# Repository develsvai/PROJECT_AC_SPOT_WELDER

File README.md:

## AC_SPOT_WELDER - 기술 분석 및 펌웨어 리팩토링

- **프로젝트 명:** 자동 트리거 기능의 AC 스팟 용접기
- **분석 대상:** 하드웨어(회로, PCB) 및 펌웨어 코드
- **문서 목적:** 원본 프로젝트의 기술적 구현 상태를 분석하고, 식별된 문제점에 대한 개선 방안과 그에 따른 최종 개선 코드를 제시함.
- 단 현재로써는 적용시킬수 있는 환경 및 조건이 안됨, 코드 관점에서의 분석

---

### **Part A. 펌웨어 코드 주요 개선점**

원본 코드는 기능 구현에 집중한 '유기체적' 코드이며, 개선된 코드는 안정성, 확장성, 유지보수성을 확보하기 위한 설계 원칙을 적용한 '구조적' 코드입니다. 각 개선점을 원본 코드와 개선된 코드의 실제 예시를 통해 비교 분석합니다.

### **1. 타이밍 제어 방식의 변경: `delay`에서 `하드웨어 타이머`로**

- **이전 코드:** 모든 시간 제어를 `delay_ms()`에 의존하며, 특히 ISR(인터럽트 서비스 루틴) 컨텍스트에서 CPU를 정지시키는 블로킹(Blocking) 방식을 사용함. 이는 시스템 반응성 저하의 주요 원인이 되는 구조적 문제점이다.

```c
// [원본 코드] ISR 내부에서 직접 delay 호출
ISR(INT0_vect)
{
    if(isr_cn == 1 & vbl>=8){
        _delay_ms(0.5);
         PORTC = 0x20; // 트리거 ON
         // CPU가 여기서 멈춰서 다음 라인으로 넘어가지 않음
         delay_ms(spot_time_hz * halfcycle); 
         PORTC = 0x00; // 트리거 OFF
         delay_ms(nbl);
         isr_cn=0;
    } 
    // ...
}
```

- **개선된 코드:** 하드웨어 Timer1을 이용해 1ms 주기의 시스템 틱(Tick)을 생성하고, 모든 시간 계산을 논블로킹(Non-blocking) 방식으로 처리함. 이를 통해 시스템은 다른 입력에 항상 반응할 수 있는 상태를 유지한다.

```c
// [개선된 코드] ISR은 플래그만 설정하고, 타이머가 시간 관리
volatile uint16_t weld_pulse_timer_ms;

// 1ms 마다 실행되는 타이머 ISR
ISR(TIMER1_COMPA_vect) {
    if (weld_pulse_timer_ms > 0) {
        weld_pulse_timer_ms--; // 0이 될 때까지 1ms씩 감소
    }
}

// 상태 머신 내부의 논블로킹 로직
case STATE_WELD_PULSE_ACTIVE:
    // 타이머가 0이 되었는지 '확인'만 할 뿐, 기다리지 않음
    if (weld_pulse_timer_ms == 0) {
        TRIAC_PORT &= ~(1 << TRIAC_PIN); // 타이머가 끝나면 트리거 OFF
        // ... 다음 상태로 전환 ...
    }
    break;
```

---

### **2. 아키텍처의 재정의: '거대 함수'에서 '상태 머신'으로**

- **이전 코드:** 하나의 거대 함수가 UI 표시, 로직 처리, 하드웨어 제어 등 다수의 책임을 갖는 구조로, 코드 흐름 파악 및 디버깅의 복잡도가 높음.

```c
// [원본 코드] 하나의 함수에 모든 로직이 얽혀 있음
void spot_action(void) {
    LCD_initialize(); // UI 초기화
    isr_init();       // 하드웨어 초기화
    // ... 데이터 로딩, UI 업데이트 ...
    while(1) { // 이 안에서 또 다른 while 루프들이 중첩됨
        while(autospot_sw==1) { /* 자동 용접 로직... */ }
        while(autospot_sw ==0) { /* 수동 용접 로직... */ }
    }
}
```

- **개선된 코드:** `enum SystemState`와 `main()` 함수의 `while(1)` 루프 내 `switch` 구문을 이용한 명시적 상태 머신(State Machine)으로 재설계함. 이는 코드의 흐름을 명확하게 하고 기능 추가의 용이성을 확보한다.

```c
// [개선된 코드] 역할이 명확히 분리된 상태 머신
typedef enum {
    STATE_IDLE_DISPLAY, STATE_WELD_PULSE_ACTIVE, STATE_MENU_SET_TIME,
    // ...
} SystemState;

int main(void) {
    initialize_all(); // 초기화는 여기서 한번만
    load_settings();
    sei();

    g_app.current_state = STATE_IDLE_DISPLAY;
    while(1) {
        switch (g_app.current_state) { // 현재 상태에 따라 분기
            case STATE_IDLE_DISPLAY:   /* IDLE 로직 처리 */ break;
            case STATE_WELD_PULSE_ACTIVE: handle_welding_logic(); break;
            case STATE_MENU_SET_TIME:   handle_menu_logic(); break;
        }
        update_display_smart(); // UI 업데이트는 항상 마지막에
    }
}
```

---

### **3. 데이터 관리의 현대화: '전역 변수'에서 '구조체'로**

- **이전 코드:** 다수의 개별 전역 변수가 코드 전체에 흩어져 있어 데이터 흐름과 연관 관계의 파악이 어려움.

```c
// [원본 코드] 의미를 알기 어려운 전역 변수들의 나열
int static_hz = 60;
int spotac_tacle=0;
int stan_flag=0;
int en_flag=1;
// ... 수십 개의 전역 변수 ...
int val,bal,nal,vbl,bbl,nbl;
```

- **개선된 코드:** `AppState_t`라는 단일 구조체(struct)를 통해 시스템의 모든 상태와 설정값을 중앙에서 관리함. `g_app.settings.time_ms`처럼 데이터의 소속과 의미가 명확해져 코드의 예측 가능성과 안정성을 높인다.

```c
// [개선된 코드] 연관 데이터끼리 묶어놓은 구조체
typedef struct {
    uint16_t time_ms;
    uint8_t  multiplier;
    // ...
} Settings_t;

typedef struct {
    SystemState current_state;
    Settings_t  settings;
    volatile uint16_t weld_pulse_timer_ms;
    // ...
} AppState_t;

volatile AppState_t g_app; // 모든 상태를 담는 유일한 전역 변수
```

---

### **4. 코드 품질과 가독성: '매직 넘버'에서 '정의된 상수'로**

- **이전 코드:** `PORTC = 0x20`과 같이 의미를 알 수 없는 숫자(매직 넘버)가 많아 가독성이 낮음.

```c
// [원본 코드] 매직 넘버 사용
#**define** S4 0x80&PINB
// ...
PORTC = 0x20;
// ...
GICR  = 0x40;
```

- **개선된 코드:** `#define`을 통해 모든 상수와 핀에 의미 있는 이름을 부여함. 이는 코드 자체를 문서처럼 만들어 가독성과 유지보수성을 극적으로 향상시킨다.

```c
// [개선된 코드] 의미 있는 이름을 가진 상수 정의
#**define** TRIAC_PORT      PORTC
#**define** TRIAC_PIN       PC5

#**define** MANUAL_SW_PIN   PB7
// ...

// 코드 내 사용 예시
TRIAC_PORT |= (1 << TRIAC_PIN); // "TRIAC 포트의 TRIAC 핀을 켠다"고 명확히 읽힘
if (!(ENCODER_PIN & (1 << MANUAL_SW_PIN))) { /* ... */ }
GICR |= (1 << INT0); // GICR 레지스터의 INT0 비트를 켠다고 명확히 읽힘
```

| 항목 | 이전 코드 (Before) | 개선된 코드 (After) |
| --- | --- | --- |
| **타이밍 제어** | `delay_ms()` 블로킹 방식 | 하드웨어 타이머 논블로킹 방식 |
| **프로그램 구조** | 거대 함수, 전역 플래그 조합 | 명확한 상태 머신 (Enum + Switch) |
| **데이터 관리** | 수많은 개별 전역 변수 | 단일 상태 구조체 (struct) |
| **가독성** | 매직 넘버 사용 | `#define`을 이용한 명명된 상수 |

---

### **Part B. 회로 및 하드웨어 분석**

### **1.1. 종합 평가**

핵심 기능 구현에 필요한 회로는 포함되어 있으나, 고전압(220V AC)을 다루는 장비로서 필수적인 안전 및 신뢰성 관련 설계가 누락되어 있음.

### **1.2. 구현된 주요 기능**

- **자동 트리거 시스템:** 풋 스위치 대신 트랜스포머 1차측의 임피던스 변화를 감지하여 용접을 시작하는 방식을 채택함.
- **TRIAC 구동부:** 유도성 부하(트랜스포머) 제어를 위해 스너버 회로(R-C)와 게이트 저항을 회로에 포함함.
- **자립형 시스템:** AC-DC 컨버터를 내장하여 외부 어댑터 없이 주 전원으로 동작하도록 설계됨.

### **1.3. 식별된 문제점 및 개선 방안**

- **문제점: 절연(Isolation) 설계 미흡**
    - **현상:** 고전압 회로와 저전압 디지털 회로 사이의 PCB 패턴 간격(연면/공간 거리)이 전기 안전 규격의 최소 요구치를 만족하지 못함. 옵토커플러 등 절연 소자 하단에 절연 성능을 높이기 위한 슬롯(Slot)이 없음.
    - **리스크:** 습기, 먼지, 전압 서지 발생 시 절연이 파괴되어 저전압 회로가 손상되거나 사용자에게 감전 위험을 초래할 수 있음.
    - **개선 방안:** 고전압부와 저전압부의 물리적 이격 거리를 최소 4mm 이상 확보하고, 절연 소자 경계에 절연 슬롯을 적용해야 함.
- **문제점: 전원 보호 회로 부재**
    - **현상:** AC 입력단에 과전류나 과전압을 방지하기 위한 부품이 설계에 포함되지 않음.
    - **리스크:** 내부 회로의 단락(쇼트)이나 외부의 전기적 충격 발생 시 회로 및 부품이 영구적으로 손상될 수 있음.
    - **개선 방안:** AC 입력단에 퓨즈(Fuse)를 직렬로 연결하여 과전류를 차단하고, 바리스터(Varistor)를 병렬로 연결하여 과전압 서지로부터 회로를 보호해야 함.
- **문제점: 전원 인가 시 간헐적 초기화 불안정**
    - **현상:** 전원을 켤 때, 간헐적으로 LCD가 정상적으로 초기화되지 않음.
    - **원인 분석:** 16MHz 크리스탈 발진자의 기동 시간 및 전원 공급 안정화 시간보다 MCU의 코드 실행 시작이 빠름. 이로 인해 불안정한 시스템 클럭 상태에서 I2C 통신이 시도되어 실패하는 것으로 분석됨.
    - **개선 방안:** AVR 퓨즈 비트(SUT, CKSEL) 설정을 변경하여 하드웨어적으로 충분한 시작 지연 시간을 확보하거나, `main()` 함수 시작부에 100ms 이상의 소프트웨어 지연 시간을 추가해야 함.

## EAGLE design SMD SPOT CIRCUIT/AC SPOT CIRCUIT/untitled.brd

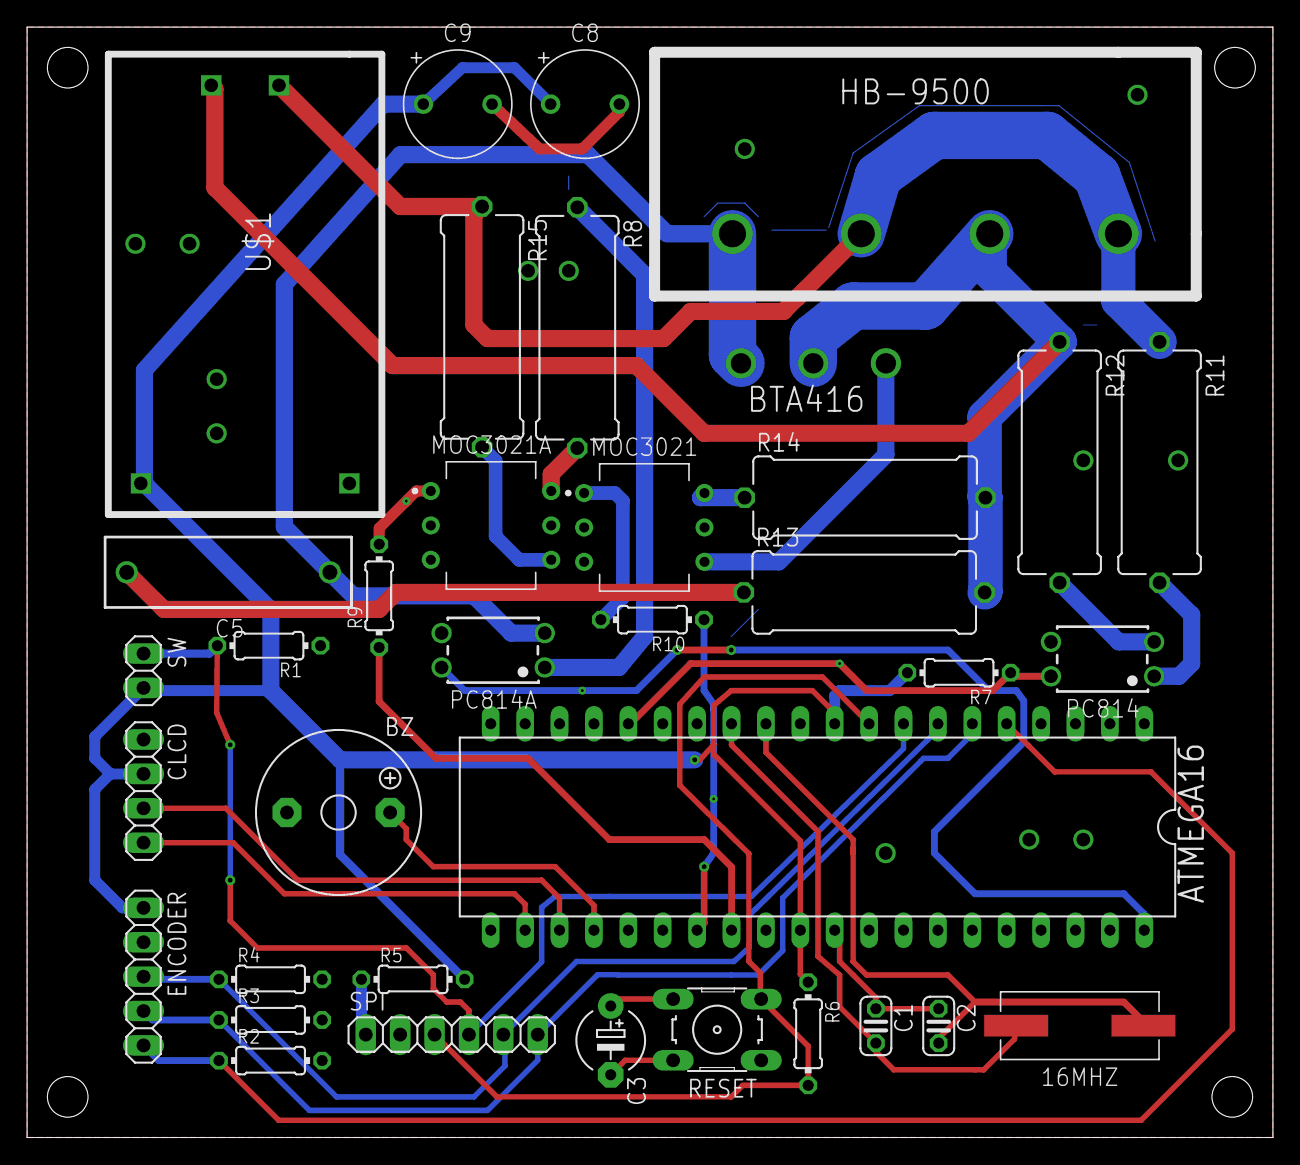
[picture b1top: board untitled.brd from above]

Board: 2 copper layers, 92.0 x 82.0 mm, 36 parts (0 on the bottom side), 32 nets.

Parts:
16MHZ: H49UP; XTAL1170X490X450N
ATMEGA16: ATMEGA16; DIL40
BTA416: BT41600B
BZ: F/TMB
C1, C2: C025-024X044
C3: 10UF; E5-5
C5: 104K; WCAP-FTX2_15X18X5X11(PXLXWXH)
C8, C9: 470uf; CAPPRD508W65D800H1100B
CLCD: 1X04
ENCODER: 1X05
HB-9500: HB-9500
MOC3021, MOC3021A: MOC3021; DIP889W53P254L940H300Q6B
PC814, PC814A: WL-OCPT-DIP4; WL-OCPT_DIP4_STANDARD
R1, R2, R3, R4: 10k; 0204/7
R5: 1k; 0204/7
R6: 4.7K; 0204/7
R7: 0204/7
R8, R13: 100; 0617/17
R9, R10: 220; 0204/7
R11, R12: 91K; 0617/17
R14, R15: 1K; 0617/17
RESET: B3F-10XX
SPI: 1X06
SW: 1X02
U$1: HLK-PM01

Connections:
(MISO)PB6: ATMEGA16.7, ENCODER.3, R4.1, SPI.5
(MOSI)PB5: ATMEGA16.6, ENCODER.4, R3.1, SPI.6
(SCK)PB7: ATMEGA16.8, R1.2, SPI.4, SW.1
(SCL)PC0: ATMEGA16.22, CLCD.4
(SDA)PC1: ATMEGA16.23, CLCD.3
(SS)PB4: ATMEGA16.5, ENCODER.5, R2.1
A0: ATMEGA16.40, PC814A.4
AC: HB-9500.P$1, HB-9500.P$3, R11.1, R15.1, U$1.AC
AC1: BTA416.P$2, HB-9500.P$2, R12.1, R13.2, R14.2, U$1.AC1
BUZZER: ATMEGA16.24, BZ.+
GND: ATMEGA16.11, ATMEGA16.31, BZ.-, C1.1, C2.1, C8.2, C9.2, CLCD.1, ENCODER.2, MOC3021.2, MOC3021.3, MOC3021A.2, MOC3021A.3, PC814.3, PC814A.3, R1.1, R2.2, R3.2, R4.2, RESET.1, SPI.2, U$1.DC-
MOC3021: ATMEGA16.27, R10.1
MOC3021A: ATMEGA16.28, R9.1
unnamed: R5.1, SPI.1
unnamed: C3.-, RESET.2
unnamed: C3.+, RESET.4
unnamed: MOC3021A.1, R9.2
unnamed: PC814.1, R11.2
unnamed: PC814.2, R12.2
unnamed: C5.2, R13.1
unnamed: BTA416.P$3, MOC3021.4
unnamed: MOC3021.6, R14.1
unnamed: MOC3021.1, R10.2
unnamed: MOC3021A.4, R15.2
unnamed: MOC3021A.6, R8.2
unnamed: PC814A.1, R8.1
PC814: ATMEGA16.16, PC814.4, R7.1
RESET: ATMEGA16.9, R6.2, RESET.3, SPI.3
TOUT: BTA416.P$1, C5.1, HB-9500.P$4, PC814A.2
VCC: ATMEGA16.10, ATMEGA16.30, C8.1, C9.1, CLCD.2, ENCODER.1, R5.2, R6.1, R7.2, SW.2, U$1.DC+
XTAL1: 16MHZ.2, ATMEGA16.13, C1.2
XTAL2: 16MHZ.1, ATMEGA16.12, C2.2

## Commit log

2023-10-16 change
2025-06-29 Refactor : 저항 번호 파일, 제로 크로싱 분석 파일 -> md 로 변경, 파일명 변경 , 코드 전체 리펙토링
2025-06-29 DS_Store 제거
2025-06-29 Refactor : DS_store 제거, image 이름 변경
2026-03-15 Reorganize project structure and normalize docs
2026-03-15 Document new architecture and simulator structure
2026-03-15 Consolidate architecture docs and project overview
2026-03-15 Restore cleaned project structure
